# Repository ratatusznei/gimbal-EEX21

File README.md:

# Sistema estabilizador de dois eixos para câmera - Gimbal

###### Autores em ordem alfabética
[Fernando](https://github.com/ratatusznei)

[Henrique](https://github.com/HenriqueKnapp)

[Robson](https://github.com/robson1622)

Foto do dispositivo montado sem o celular no suporte.

Renderização de modelo montado em computador, mostrando a placa de circuitos e as baterias internas.

## O que é?
É um dispositivo que procura manter a orientação de uma câmera ou celular fixa, compensando possíveis variações que podem ocorrer durante a gravação de um vídeo ou fotografia. O sistema estabiliza nos eixos X e Y conforme a figura:

## Como funciona?
O sistema contrói uma representação interna da orientação do dispositivo em relação à direção da gravidade com base nas leituras de dois sensores giroscópio e acelerômetro. Então utilizando de dois motores atuando sobre a orientação da câmera a gravação é estabilizada.

## Casos de uso
Além de servir como estabilizador para câmeras, esse sistema pode ser readequado para uso em robôs sensíveis à orientação, drones ou em aplicações de realidade virtual capturando a orientação de um objeto no mundo real.

## Mais detalhes
Para mais detalhes e referências sobre o projeto, verifique o [relatório final nesse mesmo repositório](https://github.com/ratatusznei/gimbal-EEX21/blob/master/relatorio/pdfs/EEX21_Equipe5_Relatorio_EstabilizadorDeDoisEixosPraCameras.pdf).

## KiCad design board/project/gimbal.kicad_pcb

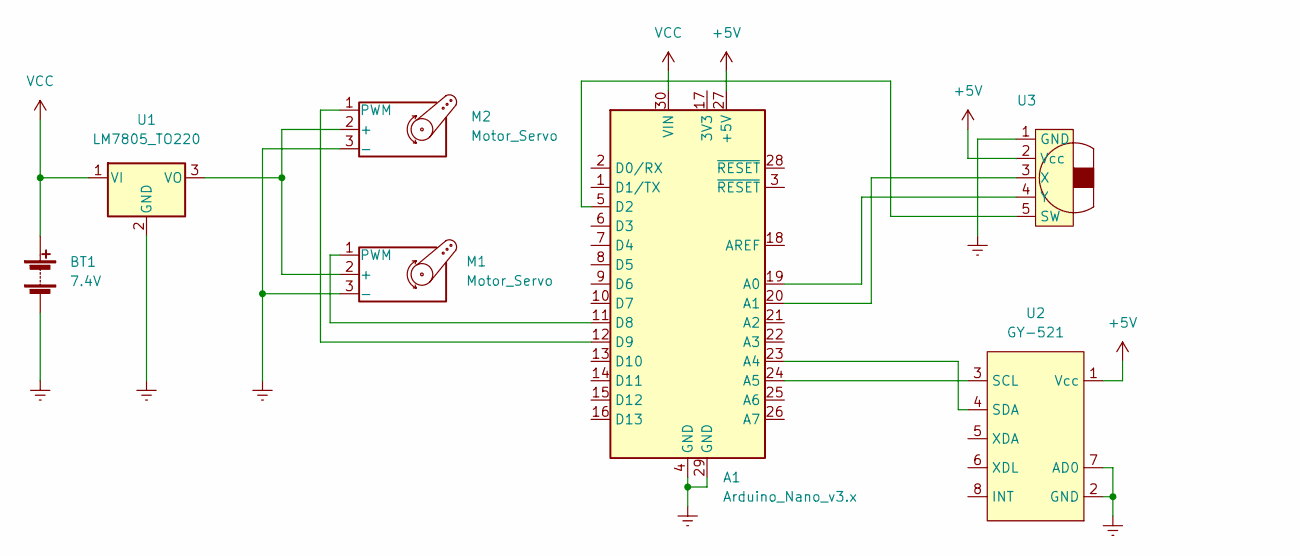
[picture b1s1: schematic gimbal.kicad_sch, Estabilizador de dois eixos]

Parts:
A1: Arduino_Nano_v3.x; Arduino_Nano
BT1: 7.4V; PinHeader_1x02_P2.54mm_Vertical
M1, M2: Motor_Servo; PinHeader_1x03_P2.54mm_Vertical
U1: LM7805_TO220; TO-220-3_Vertical
U2: GY-521; PinSocket_1x08_P2.54mm_Vertical
U3: (no value)

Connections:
+5V: A1.27 (+5V), U2.1 (Vcc), U3.2 (Vcc)
Earth: A1.4 (GND), A1.29 (GND), BT1.2 (-), M1.3 (-), M2.3 (-), U1.2 (GND), U2.2 (GND), U2.7 (AD0), U3.1 (GND)
unnamed: A1.5 (D2), U3.5 (SW)
unnamed: A1.11 (D8), M1.1 (PWM)
unnamed: A1.12 (D9), M2.1 (PWM)
unnamed: A1.19 (A0), U3.4 (Y)
unnamed: A1.20 (A1), U3.3 (X)
unnamed: A1.23 (A4), U2.4 (SDA)
unnamed: A1.24 (A5), U2.3 (SCL)
unnamed: M1.2 (+), M2.2 (+), U1.3 (VO)
VCC: A1.30 (VIN), BT1.1 (+), U1.1 (VI)

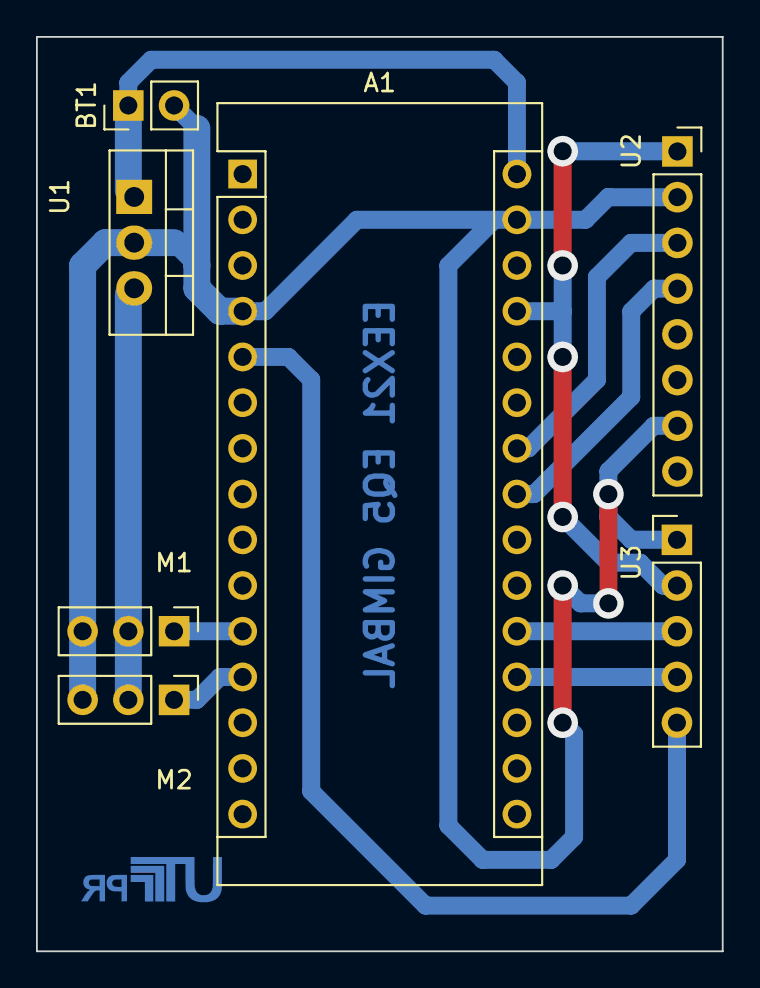
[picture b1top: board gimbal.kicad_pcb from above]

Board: 2 copper layers, 38.1 x 50.8 mm, 8 parts (1 on the bottom side), 11 nets.

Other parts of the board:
Logo: LOGO; utfpr

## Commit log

2022-04-10 init
2022-04-11 teapot
2022-04-11 joystick + servos
2022-04-14 logo + name + smaller board
2022-04-14 directories
2022-04-14 schematic
2022-05-02 fix joystick power input
2022-05-12 move source to gimbal-arduino
2022-05-15 begin files
2022-05-15 testing mpu6050_light lib
2022-05-16 add 2nd servo
2022-05-16 imu class + makefile
2022-05-16 add servo controller
2022-05-16 Changed ctors for begin methods
2022-05-28 filtro de media, ultimos 5 valores
2022-05-30 read joystick
2022-07-06 relatorio final
2022-07-06 cleanup
2022-07-06 adiona arquivos stl da estrutura 3d
2022-07-06 readme
2022-07-06 Add autores
